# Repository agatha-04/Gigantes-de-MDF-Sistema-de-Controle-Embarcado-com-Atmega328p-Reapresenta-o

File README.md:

# Gigantes-de-MDF-Sistema-de-Controle-Embarcado-com-Atmega328p-Reapresenta-o
Firmware, Eletrônica e Documentação Técnica do projeto final da disciplina de Programação de Hardware - 2025.

## Descrição Geral
Esse projeto implementa o sistema eletrônico e programação em C ao robô do projeto final da disciplina Programação de Hardware (2025).
Ele deve:
* Se mover de acordo com os comandos enviados pelo celular via bluetooth (módulo HC-05);
* Controlar os motores por via PWM;
* Detectar impactos do laser inimigo através de um LDR;
* Disparar sua própria arma laser de 1 em 1 segundo;
* Registrar danos (causados pelo laser inimigo) através de LEDs que representam as vidas;
* Reagir ao ser atingido (giro de 180º, perda de uma vida, pausa de 5 segundos);
* Parar o sistema inteiro após a perda das três vidas, reiniciando após apertar o botão de reset.

## Objetivos
* Aplicar conceitos de programação de hardware usando o microcontrolador ATmega328p.
* Projetar um circuito completo de acionamento de motores.
* Implementar controle PWM para movimentação.
* Implementar timers para disparo do laser e rotina de 1 segundo.
* Programar rotinas de interrupção para o botão reset das vidas.
* Criar documentação com o Doxygen.
* Disponilizar todo o código em repositório GitHub.

## Componentes Eletrônicos Usados no Projeto
* 1 microcontrolador do tipo ATmega328p.
* 1 diodo laser de 5V/5mW.
* 1 LDR de 20 milímetros.
* 3 LEDs azuis 10 milímetros.
* 1 CI de ponte H L293d.
* 2 motores DC com faixa de operação de 3V-6V.
* 1 módulo bluetooth HC-05 (para comunicação do controle no celular com o atmega que controla o carrinho).
* Regulador de tensão de 5V (LM7805).
* Regulador de tensão dd 6V (LM7806).
* 2 baterias de 9V.

## Como Testar
- **1.** Gravar o arquivo car_main_final.ino.hex no respectivo microcontrolador.
- **2.** Conectar as baterias ao robô.
- **3.** Testar as respectivas funções:
     * Giro no eixo;
     * PWM dos motores;
     * Disparo do laser:
     * Resposta ao laser inimigo;
     * LEDs de vida;
     * Botão de reset.

## Autores
* **Autor(a):** Agatha Nicole Marques Fávaro - **RA:** 231335
* **Autor(a):** Mykaella Scarllet de Lemos Santana - **RA:** 233508
* **Autor(a):** Rafael Ribeiro de Lima - **RA:** 226326
* Universidade Santa Cecília - Engenharia da Computação
* **Disciplina:** Programação de Hardware - 2/2025
* **Professor(a):** Sérgio Schina de Andrade

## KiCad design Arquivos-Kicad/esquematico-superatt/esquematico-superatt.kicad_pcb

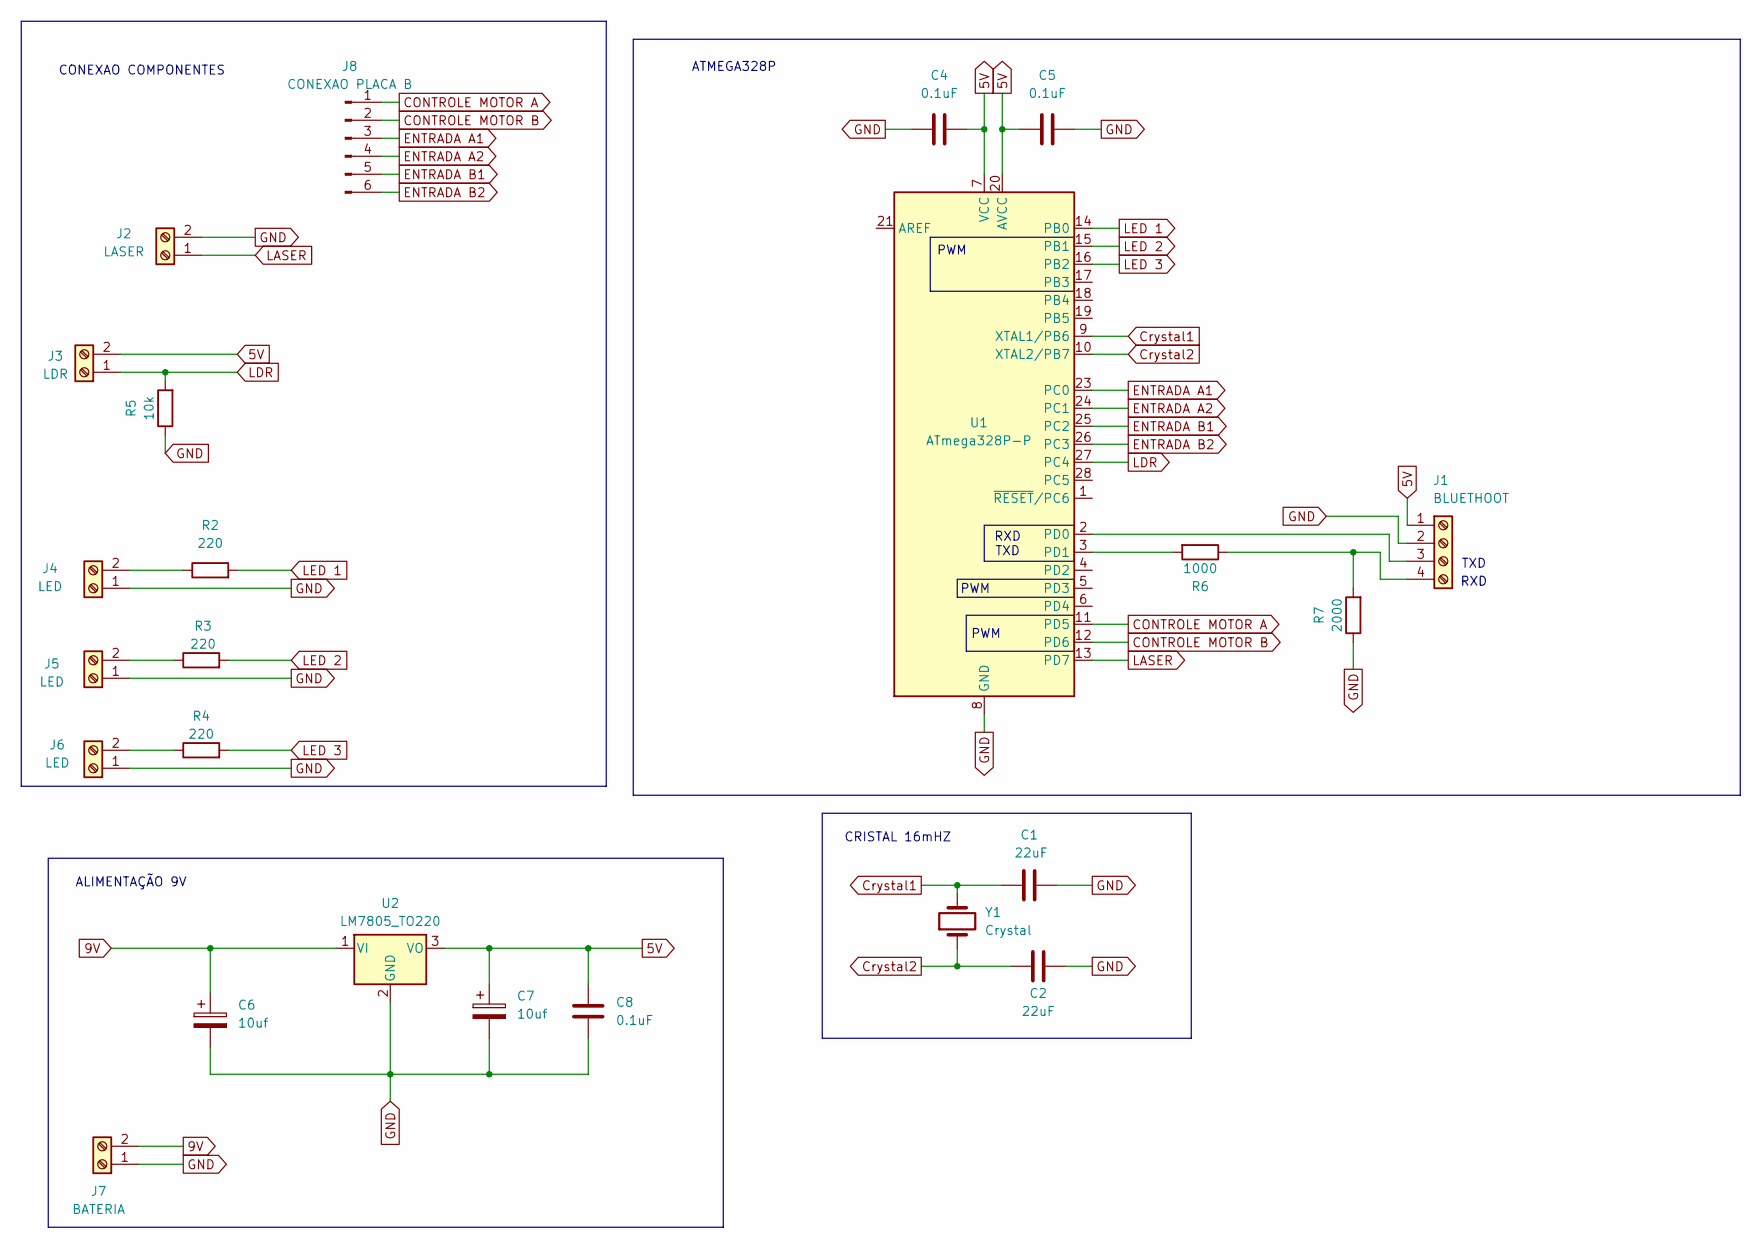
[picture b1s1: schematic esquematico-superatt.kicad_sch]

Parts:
C1, C2: 22uF; CP_Radial_D7.5mm_P2.50mm
C4, C5, C8: 0.1uF; CP_Radial_D7.5mm_P2.50mm
C6, C7: 10uf; CP_Radial_D7.5mm_P2.50mm
J1: BLUETHOOT; TerminalBlock_bornier-4_P5.08mm
J2: LASER; TerminalBlock_bornier-2_P5.08mm
J3: LDR; TerminalBlock_bornier-2_P5.08mm
J4, J5, J6: LED; TerminalBlock_bornier-2_P5.08mm
J7: BATERIA; TerminalBlock_bornier-2_P5.08mm
J8: CONEXAO PLACA B; PinHeader_1x06_P2.54mm_Vertical
R2, R3, R4: 220; R_Axial_DIN0204_L3.6mm_D1.6mm_P7.62mm_Horizontal
R5: 10k; R_Axial_DIN0204_L3.6mm_D1.6mm_P7.62mm_Horizontal
R6: 1000; R_Axial_DIN0204_L3.6mm_D1.6mm_P7.62mm_Horizontal
R7: 2000; R_Axial_DIN0204_L3.6mm_D1.6mm_P7.62mm_Horizontal
U1: ATmega328P-P; DIP-28_W7.62mm
U2: LM7805_TO220; TO-220-3_Vertical
Y1: Crystal; Crystal_HC49-U_Vertical

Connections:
5V: C4.1, C5.2, C7.1, C8.2, J1.1, J3.2, U1.7 (VCC), U1.20 (AVCC), U2.3 (VO)
9V: C6.1, J7.2, U2.1 (VI)
CONTROLE MOTOR A: J8.1, U1.11 (PD5)
CONTROLE MOTOR B: J8.2, U1.12 (PD6)
Crystal1: C1.1, U1.9 (XTAL1/PB6), Y1.2
Crystal2: C2.1, U1.10 (XTAL2/PB7), Y1.1
ENTRADA A1: J8.3, U1.23 (PC0)
ENTRADA A2: J8.4, U1.24 (PC1)
ENTRADA B1: J8.5, U1.25 (PC2)
ENTRADA B2: J8.6, U1.26 (PC3)
GND: C1.2, C2.2, C4.2, C5.1, C6.2, C7.2, C8.1, J1.2, J2.2, J4.1, J5.1, J6.1, J7.1, R5.1, R7.1, U1.8 (GND), U1.22 (GND), U2.2 (GND)
LASER: J2.1, U1.13 (PD7)
LDR: J3.1, R5.2, U1.27 (PC4)
LED 1: R2.2, U1.14 (PB0)
LED 2: R3.2, U1.15 (PB1)
LED 3: R4.2, U1.16 (PB2)
unnamed: J1.3, U1.2 (PD0)
unnamed: J1.4, R6.1, R7.2
unnamed: J4.2, R2.1
unnamed: J5.2, R3.1
unnamed: J6.2, R4.1
unnamed: R6.2, U1.3 (PD1)

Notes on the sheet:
TXD
PWM
ALIMENTAÇÃO 9V
RXD
ATMEGA328P
CONEXAO COMPONENTES
RXD TXD
CRISTAL 16mHZ

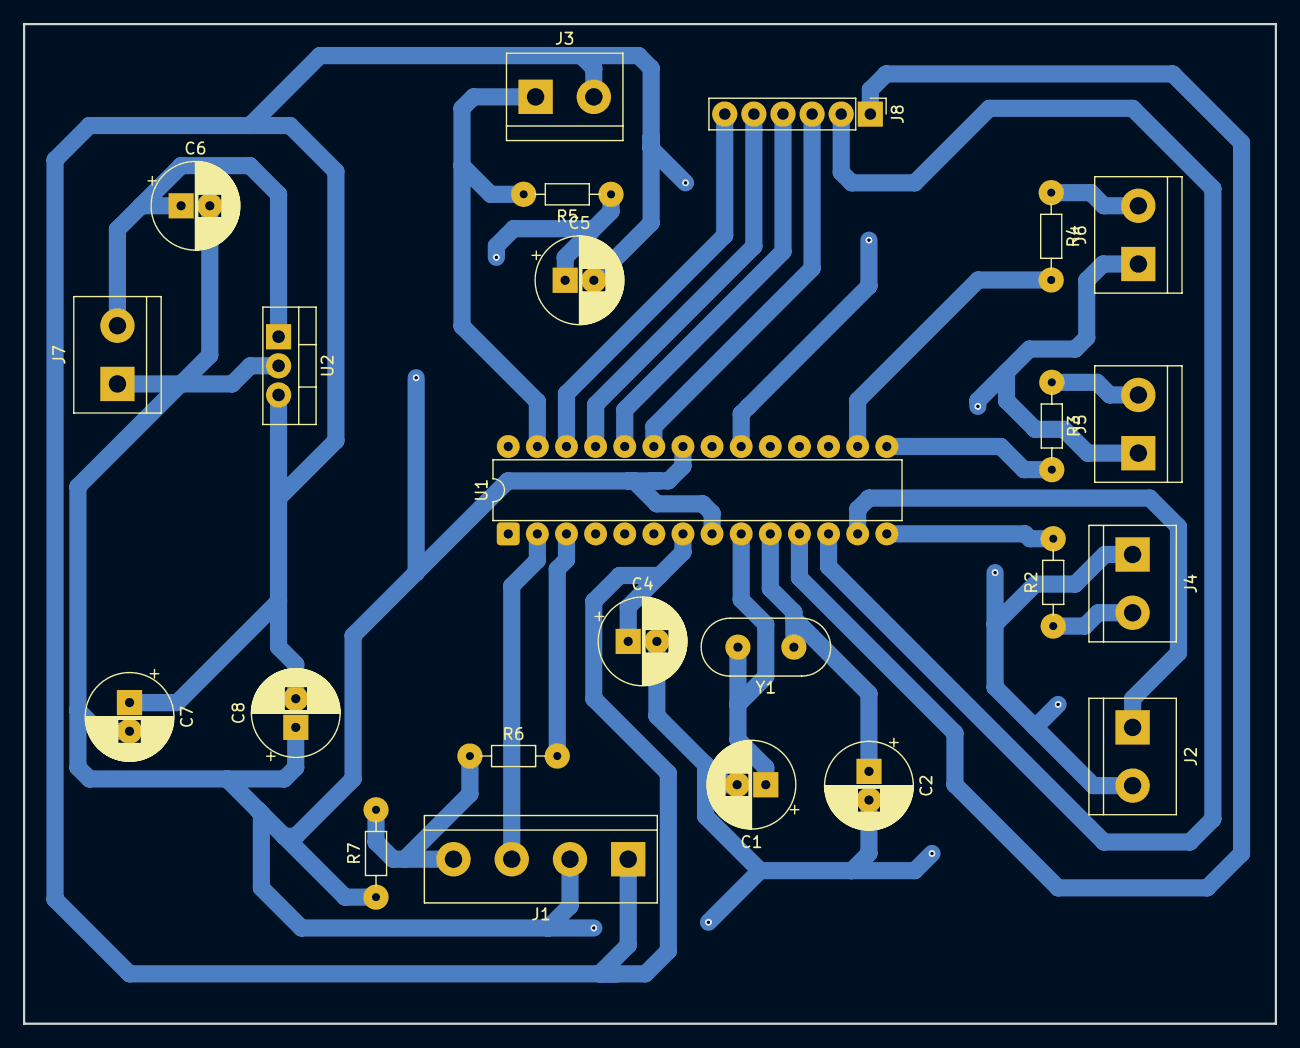
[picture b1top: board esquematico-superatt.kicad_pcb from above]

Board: 2 copper layers, 109.2 x 87.2 mm, 24 parts (0 on the bottom side), 22 nets.

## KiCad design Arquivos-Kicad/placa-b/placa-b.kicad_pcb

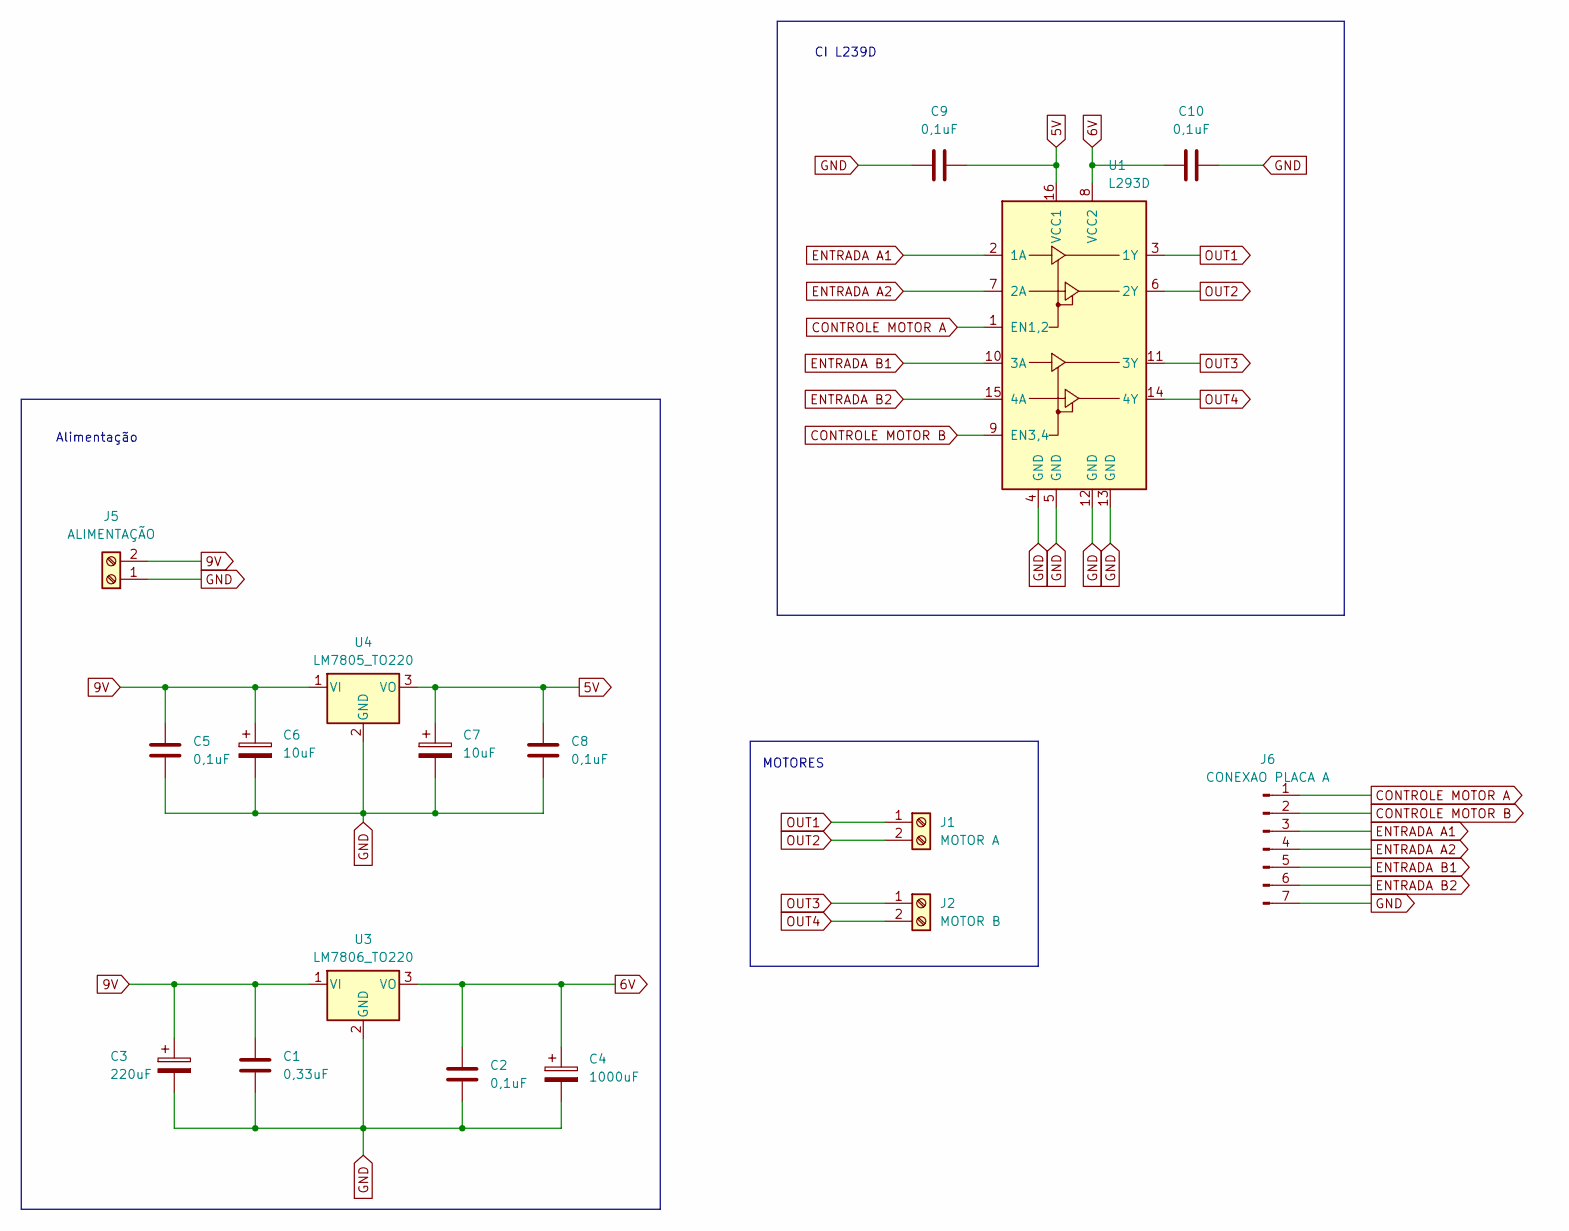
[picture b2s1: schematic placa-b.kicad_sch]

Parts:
C1: 0,33uF; CP_Radial_D7.5mm_P2.50mm
C2, C5, C8, C9, C10: 0,1uF; CP_Radial_D7.5mm_P2.50mm
C3: 220uF; CP_Radial_D7.5mm_P2.50mm
C4: 1000uF; CP_Radial_D7.5mm_P2.50mm
C6, C7: 10uF; CP_Radial_D7.5mm_P2.50mm
J1: MOTOR A; TerminalBlock_bornier-2_P5.08mm
J2: MOTOR B; TerminalBlock_bornier-2_P5.08mm
J5: ALIMENTAÇÃO; TerminalBlock_bornier-2_P5.08mm
J6: CONEXAO PLACA A; PinHeader_1x07_P2.54mm_Vertical
U1: L293D; DIP-16_W7.62mm
U3: LM7806_TO220; TO-220-3_Vertical
U4: LM7805_TO220; TO-220-3_Vertical

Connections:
5V: C7.1, C8.1, C9.2, U1.16 (VCC1), U4.3 (VO)
6V: C2.1, C4.1, C10.1, U1.8 (VCC2), U3.3 (VO)
9V: C1.1, C3.1, C5.1, C6.1, J5.2, U3.1 (VI), U4.1 (VI)
CONTROLE MOTOR A: J6.1, U1.1 (EN1,2)
CONTROLE MOTOR B: J6.2, U1.9 (EN3,4)
ENTRADA A1: J6.3, U1.2 (1A)
ENTRADA A2: J6.4, U1.7 (2A)
ENTRADA B1: J6.5, U1.10 (3A)
ENTRADA B2: J6.6, U1.15 (4A)
GND: C1.2, C2.2, C3.2, C4.2, C5.2, C6.2, C7.2, C8.2, C9.1, C10.2, J5.1, J6.7, U1.4 (GND), U1.5 (GND), U1.12 (GND), U1.13 (GND), U3.2 (GND), U4.2 (GND)
OUT1: J1.1, U1.3 (1Y)
OUT2: J1.2, U1.6 (2Y)
OUT3: J2.1, U1.11 (3Y)
OUT4: J2.2, U1.14 (4Y)

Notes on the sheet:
MOTORES
Alimentação
CI L239D

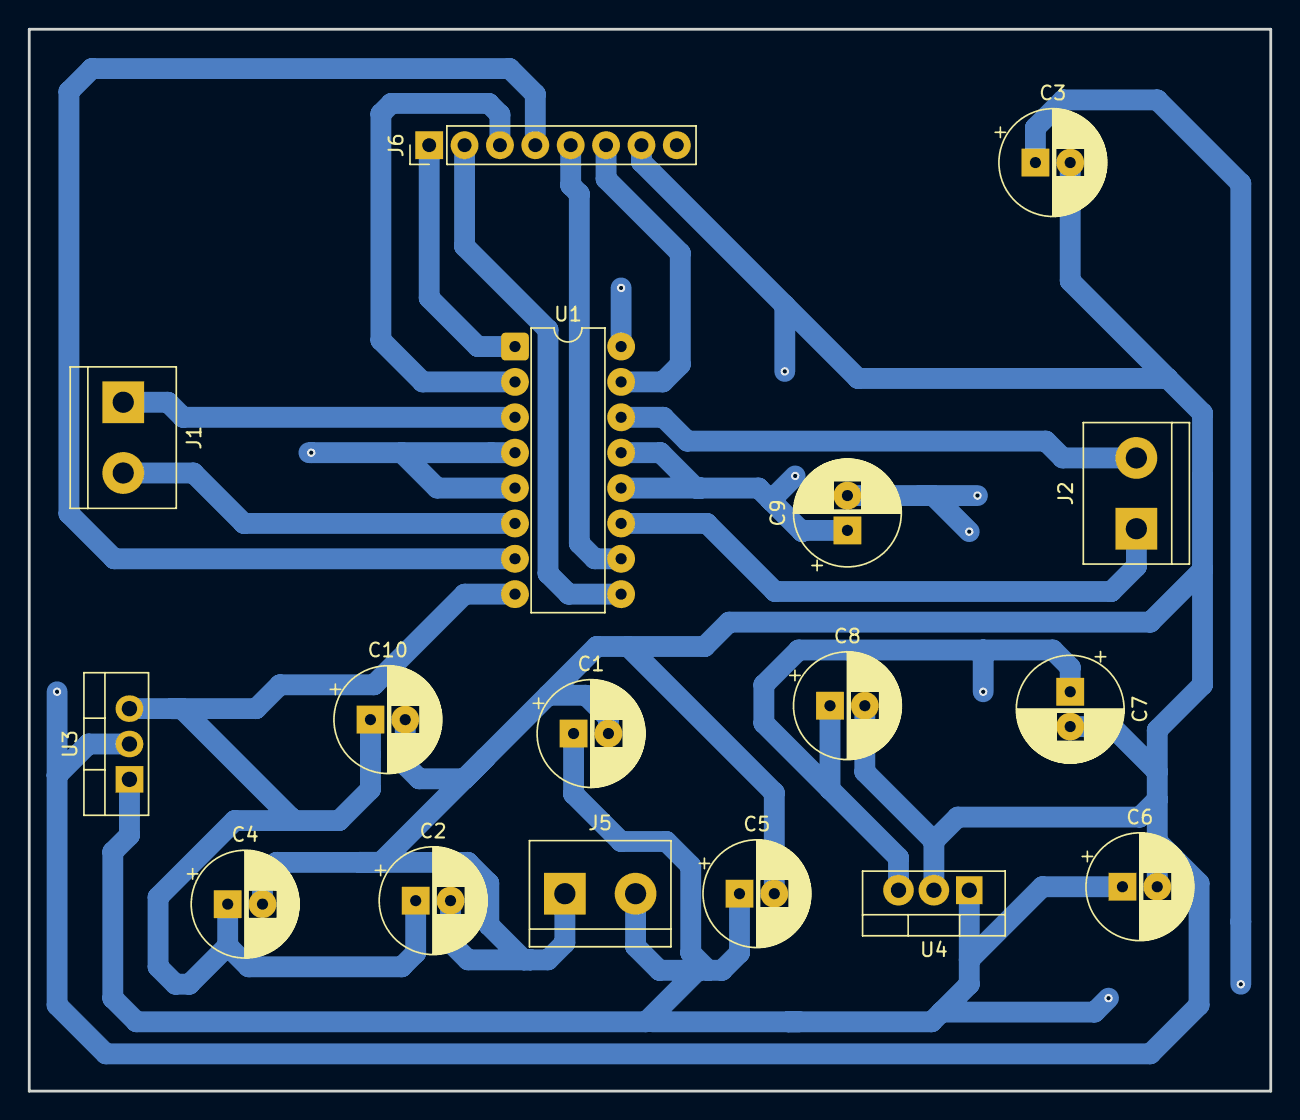
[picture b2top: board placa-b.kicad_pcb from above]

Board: 2 copper layers, 89.2 x 76.2 mm, 17 parts (0 on the bottom side), 14 nets.

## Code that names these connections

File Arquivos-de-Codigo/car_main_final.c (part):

/*
  car_main_final.c
  ATmega328P, F_CPU = 16MHz
  Integra PWM (OC0A/OC0B) para EN pins, ADC LDR, HC-05 serial, e lógica de "vidas".
  Pinagem:
  - LEDs: PB0, PB1, PB2
  - Laser: PD7
  - LDR: ADC4 (A4)
  - L293D:
      Enable1/2 -> PD5 (OC0B)
      Enable3/4 -> PD6 (OC0A)
      1A -> PC0
      2A -> PC1
      3A -> PC2
      4A -> PC3
  - HC-05:
      TX (HC-05) -> PD0 (RXD)
      RX (HC-05) -> PD1 (TXD)
*/
 
#define F_CPU 16000000UL
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 
/* ---------- CONFIGURÁVEIS ---------- */
#define ADC_THRESHOLD 950           // ajuste: valor ADC (0-1023) que conta como "luz forte"
#define DEBOUNCE_MS 50              // tempo de debounce da leitura do LDR
#define LASER_BLINK_INTERVAL_MS 1000UL
#define ROTATE_TIME_MS 700UL        // tempo aproximado para girar ~180° (ajuste conforme seu chassi)
#define PAUSE_AFTER_ROTATE_MS 5000UL // 5 segundos parado
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/* Pinos (macros) */
#define LED_PORT PORTB
#define LED_DDR  DDRB
#define LED_PIN0 PB0
#define LED_PIN1 PB1
#define LED_PIN2 PB2
 
#define LASER_PORT PORTD
#define LASER_DDR  DDRD
#define LASER_PIN PD7
 
/* Motor control on PORTC */
#define MOT_PORT PORTC
#define MOT_DDR  DDRC
#define M1_IN1 PC0
#define M1_IN2 PC1
#define M2_IN1 PC2
#define M2_IN2 PC3
 
/* Enables on PD5 PD6 (OC0B, OC0A) */
#define ENABLE_PORT PORTD
#define ENABLE_DDR  DDRD
#define EN12 PD5  // OC0B
#define EN34 PD6  // OC0A
 
/* USART baud */
#define BAUD 9600
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/* Inicializa Timer0 para PWM e contagem (Fast PWM, prescaler 64).
   Configura também OC0A/OC0B para saída PWM. */
void timer0_pwm_millis_init(void) {
    // PD6 = OC0A, PD5 = OC0B -> definir como outputs
    DDRD |= (1<<EN12) | (1<<EN34);
 
   
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 
/* Ajusta PWM (0..255) para ambas enables */
void motors_pwm(uint8_t val) {
    OCR0A = val; // PD6 -> EN34
    OCR0B = val; // PD5 -> EN12
}
 
/* Inicializa USART (9600, 8N1) */
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    LED_PORT |= (1<<LED_PIN0) | (1<<LED_PIN1) | (1<<LED_PIN2);
}
void led_off_index(uint8_t idx) {
    // idx 0 -> PB0, 1 -> PB1, 2 -> PB2
    if (idx == 0) LED_PORT &= ~(1<<LED_PIN0);
    else if (idx == 1) LED_PORT &= ~(1<<LED_PIN1);
    else if (idx == 2) LED_PORT &= ~(1<<LED_PIN2);
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    if (lives == 0) return;
    reaction_active = true;
 
    // Apaga um LED: usa ordem PB0 -> PB1 -> PB2
    uint8_t idx_to_turn_off = 3 - lives; // se lives=3 -> idx=0; lives=2 -> idx=1; lives=1 -> idx=2
    led_off_index(idx_to_turn_off);
 
    // Laser off (manter desligado durante reação)
    LASER_PORT &= ~(1<<LASER_PIN);
 
    // Sequência: girar 180, pausar, voltar
    rotate_180_and_back();
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    // começa LEDs off; depois ligamos
    LED_PORT &= ~((1<<LED_PIN0)|(1<<LED_PIN1)|(1<<LED_PIN2));
 
    LASER_DDR |= (1<<LASER_PIN);
    LASER_PORT &= ~(1<<LASER_PIN);
 
    // motor input pins on PORTC
    MOT_DDR |= (1<<M1_IN1)|(1<<M1_IN2)|(1<<M2_IN1)|(1<<M2_IN2);
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 
    uint32_t last_laser_toggle = millis();
    bool laser_state = true;
    LASER_PORT |= (1<<LASER_PIN); // laser ligado inicialmente
    last_laser_toggle = millis();
 
    uint32_t last_ldr_sample = 0;
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            uint32_t now = millis();
            if (now - last_laser_toggle >= LASER_BLINK_INTERVAL_MS) {
                laser_state = !laser_state;
                if (laser_state) LASER_PORT |= (1<<LASER_PIN);
                else LASER_PORT &= ~(1<<LASER_PIN);
                last_laser_toggle = now;
            }
        } else {
            // se sistema bloqueado ou em reação, manter laser desligado
            LASER_PORT &= ~(1<<LASER_PIN);
        }
 
        // 2) ler UART não-bloqueante
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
